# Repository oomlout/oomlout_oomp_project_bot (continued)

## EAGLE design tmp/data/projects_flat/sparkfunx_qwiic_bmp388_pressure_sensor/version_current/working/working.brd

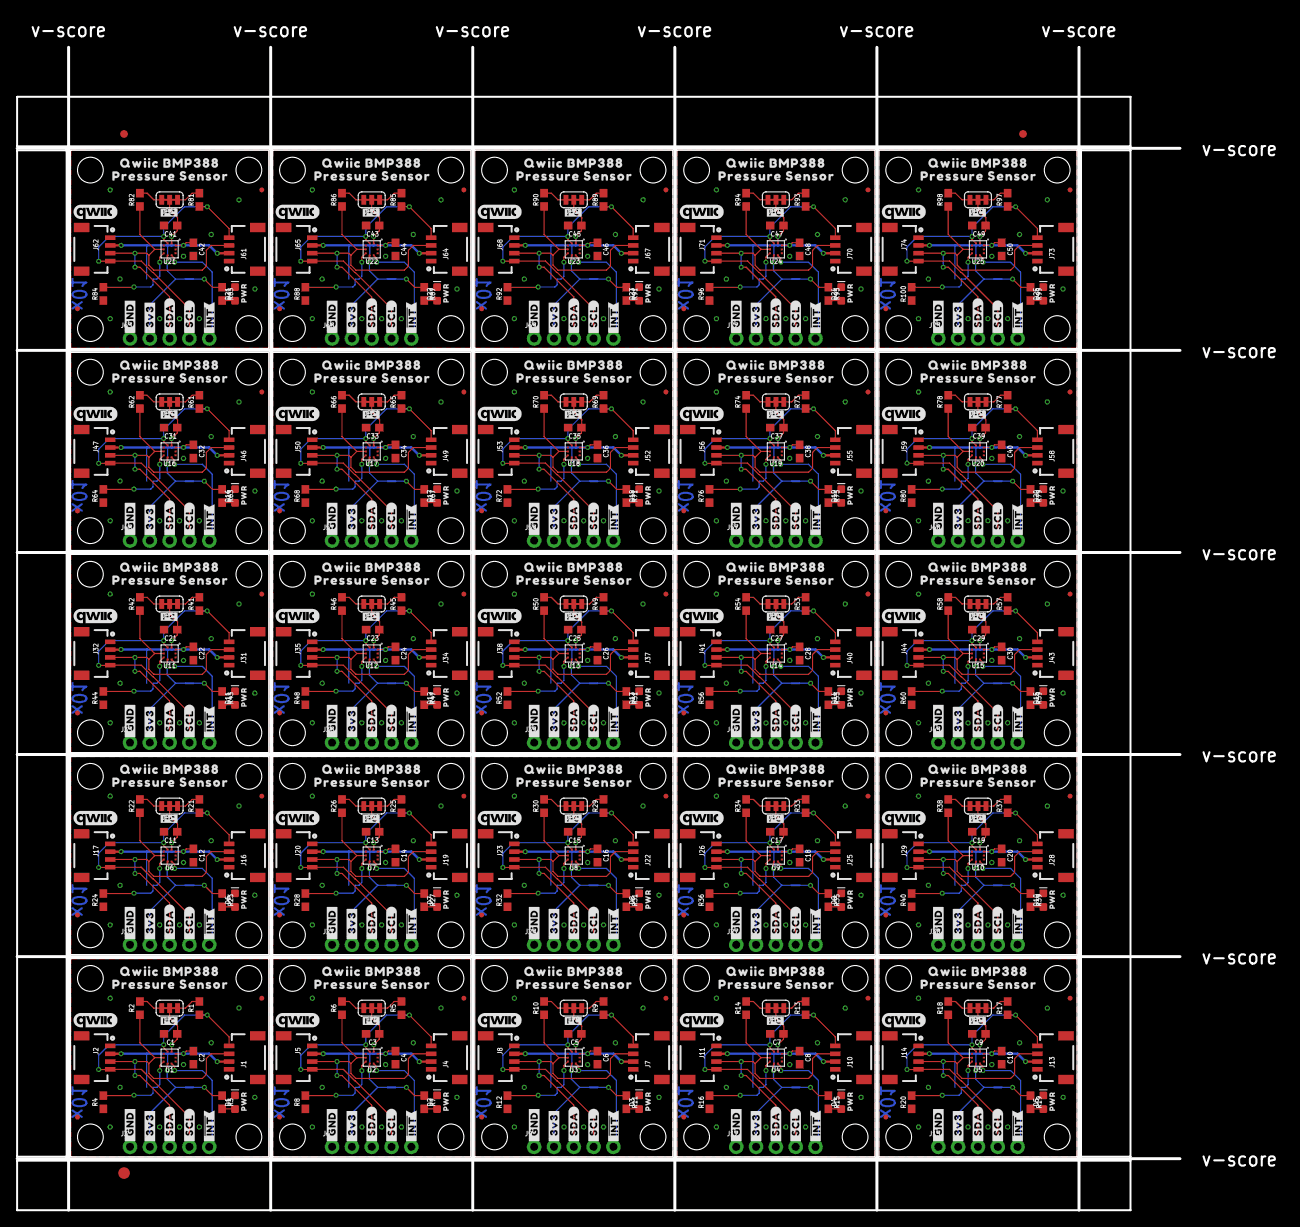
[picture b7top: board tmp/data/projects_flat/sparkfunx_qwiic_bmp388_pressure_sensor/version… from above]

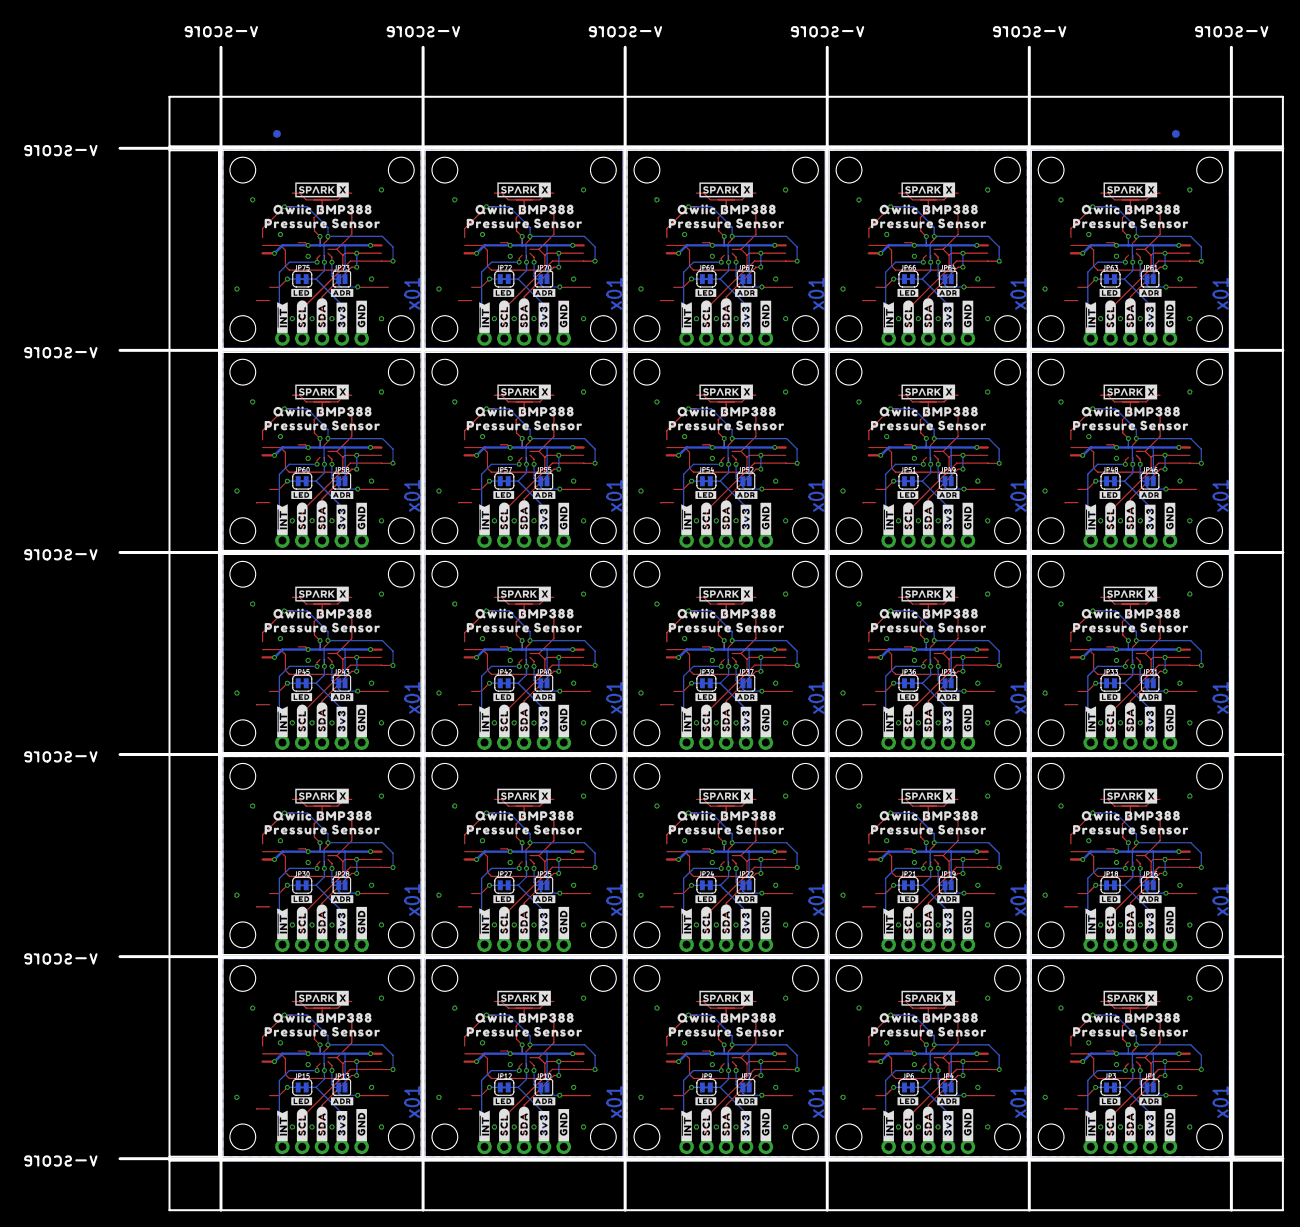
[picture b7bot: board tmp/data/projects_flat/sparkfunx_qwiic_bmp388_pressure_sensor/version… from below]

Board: 2 copper layers, 149.1 x 149.1 mm, 955 parts (302 on the bottom side), 250 nets.

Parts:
A1, A2, A3, A4, A5, A6, A7, A8, A9, A10, A11, A12, A13, A14, A15, A16, A17, A18, A19, A20, A21, A22, A23, A24, A25: QWIIC_BOARD_OUTLINEH; QWIIC_BOARD_MOUNT_HOLES
C1, C2, C3, C4, C5, C6, C7, C8, C9, C10, C11, C12, C13, C14, C15, C16, C17, C18, C19, C20, C21, C22, C23, C24, C25, C26, C27, C28, C29, C30, C31, C32, C33, C34, C35, C36, C37, C38, C39, C40, C41, C42, C43, C44, C45, C46, C47, C48, C49, C50: 0.1uF; 0603
D1, D2, D3, D4, D5, D6, D7, D8, D9, D10, D11, D12, D13, D14, D15, D16, D17, D18, D19, D20, D21, D22, D23, D24, D25: RED; LED-0603
E$1, E$2, E$3, E$4: FIDUCIAL-1X2
E$5: FIDUCIAL-1.5X3
FD1, FD2, FD3, FD4, FD5, FD6, FD7, FD8, FD9, FD10, FD11, FD12, FD13, FD14, FD15, FD16, FD17, FD18, FD19, FD20, FD21, FD22, FD23, FD24, FD25, FD26, FD27, FD28, FD29, FD30, FD31, FD32, FD33, FD34, FD35, FD36, FD37, FD38, FD39, FD40, FD41, FD42, FD43, FD44, FD45, FD46, FD47, FD48, FD49, FD50: FIDUCIALUFIDUCIAL; FIDUCIAL-MICRO
FRAME1, FRAME2, FRAME3, FRAME4, FRAME5, FRAME6, FRAME7, FRAME8, FRAME9, FRAME10, FRAME11, FRAME12, FRAME13, FRAME14, FRAME15, FRAME16, FRAME17, FRAME18, FRAME19, FRAME20, FRAME21, FRAME22, FRAME23, FRAME24, FRAME25: FRAME-LETTERNO_PACKAGE; DUMMY
J1, J2, J4, J5, J7, J8, J10, J11, J13, J14, J16, J17, J19, J20, J22, J23, J25, J26, J28, J29, J31, J32, J34, J35, J37, J38, J40, J41, J43, J44, J46, J47, J49, J50, J52, J53, J55, J56, J58, J59, J61, J62, J64, J65, J67, J68, J70, J71, J73, J74: 1X04_1MM_RA
J3, J6, J9, J12, J15, J18, J21, J24, J27, J30, J33, J36, J39, J42, J45, J48, J51, J54, J57, J60, J63, J66, J69, J72, J75: 1X05_NO_SILK
JP1, JP4, JP7, JP10, JP13, JP16, JP19, JP22, JP25, JP28, JP31, JP34, JP37, JP40, JP43, JP46, JP49, JP52, JP55, JP58, JP61, JP64, JP67, JP70, JP73: SMT-JUMPER_2_NO_SILK
JP2, JP5, JP8, JP11, JP14, JP17, JP20, JP23, JP26, JP29, JP32, JP35, JP38, JP41, JP44, JP47, JP50, JP53, JP56, JP59, JP62, JP65, JP68, JP71, JP74: SMT-JUMPER_3_2-NC_TRACE_SILK
JP3, JP6, JP9, JP12, JP15, JP18, JP21, JP24, JP27, JP30, JP33, JP36, JP39, JP42, JP45, JP48, JP51, JP54, JP57, JP60, JP63, JP66, JP69, JP72, JP75: SMT-JUMPER_2_NC_TRACE_SILK
R1, R2, R5, R6, R9, R10, R13, R14, R17, R18, R21, R22, R25, R26, R29, R30, R33, R34, R37, R38, R41, R42, R45, R46, R49, R50, R53, R54, R57, R58, R61, R62, R65, R66, R69, R70, R73, R74, R77, R78, R81, R82, R85, R86, R89, R90, R93, R94, R97, R98: 2.2k; 0603
R3, R7, R11, R15, R19, R23, R27, R31, R35, R39, R43, R47, R51, R55, R59, R63, R67, R71, R75, R79, R83, R87, R91, R95, R99: 1k; 0603
R4, R8, R12, R16, R20, R24, R28, R32, R36, R40, R44, R48, R52, R56, R60, R64, R68, R72, R76, R80, R84, R88, R92, R96, R100: 10k; 0603
U1, U2, U3, U4, U5, U6, U7, U8, U9, U10, U11, U12, U13, U14, U15, U16, U17, U18, U19, U20, U21, U22, U23, U24, U25: BMP388BMP388; LGA-10(2X2)
U$1, U$13, U$21, U$33, U$41, U$53, U$61, U$73, U$81, U$93, U$101, U$113, U$121, U$133, U$141, U$153, U$161, U$173, U$181, U$193, U$201, U$213, U$221, U$233, U$241, U$253, U$261, U$273, U$281, U$293, U$301, U$313, U$321, U$333, U$341, U$353, U$361, U$373, U$381, U$393, U$401, U$413, U$421, U$433, U$441, U$453, U$461, U$473, U$481, U$493: #_GND#3889
U$2, U$12, U$22, U$32, U$42, U$52, U$62, U$72, U$82, U$92, U$102, U$112, U$122, U$132, U$142, U$152, U$162, U$172, U$182, U$192, U$202, U$212, U$222, U$232, U$242, U$252, U$262, U$272, U$282, U$292, U$302, U$312, U$322, U$332, U$342, U$352, U$362, U$372, U$382, U$392, U$402, U$412, U$422, U$432, U$442, U$452, U$462, U$472, U$482, U$492: #_3V3#3890
U$3, U$11, U$23, U$31, U$43, U$51, U$63, U$71, U$83, U$91, U$103, U$111, U$123, U$131, U$143, U$151, U$163, U$171, U$183, U$191, U$203, U$211, U$223, U$231, U$243, U$251, U$263, U$271, U$283, U$291, U$303, U$311, U$323, U$331, U$343, U$351, U$363, U$371, U$383, U$391, U$403, U$411, U$423, U$431, U$443, U$451, U$463, U$471, U$483, U$491: #_SDA#3891
U$4, U$10, U$24, U$30, U$44, U$50, U$64, U$70, U$84, U$90, U$104, U$110, U$124, U$130, U$144, U$150, U$164, U$170, U$184, U$190, U$204, U$210, U$224, U$230, U$244, U$250, U$264, U$270, U$284, U$290, U$304, U$310, U$324, U$330, U$344, U$350, U$364, U$370, U$384, U$390, U$404, U$410, U$424, U$430, U$444, U$450, U$464, U$470, U$484, U$490: #_SCL#3892
U$5, U$9, U$25, U$29, U$45, U$49, U$65, U$69, U$85, U$89, U$105, U$109, U$125, U$129, U$145, U$149, U$165, U$169, U$185, U$189, U$205, U$209, U$225, U$229, U$245, U$249, U$265, U$269, U$285, U$289, U$305, U$309, U$325, U$329, U$345, U$349, U$365, U$369, U$385, U$389, U$405, U$409, U$425, U$429, U$445, U$449, U$465, U$469, U$485, U$489: #_#INT##3893
U$6, U$26, U$46, U$66, U$86, U$106, U$126, U$146, U$166, U$186, U$206, U$226, U$246, U$266, U$286, U$306, U$326, U$346, U$366, U$386, U$406, U$426, U$446, U$466, U$486: #I�C#1
U$7, U$27, U$47, U$67, U$87, U$107, U$127, U$147, U$167, U$187, U$207, U$227, U$247, U$267, U$287, U$307, U$327, U$347, U$367, U$387, U$407, U$427, U$447, U$467, U$487: #ADR#2
U$8, U$28, U$48, U$68, U$88, U$108, U$128, U$148, U$168, U$188, U$208, U$228, U$248, U$268, U$288, U$308, U$328, U$348, U$368, U$388, U$408, U$428, U$448, U$468, U$488: #LED#0
U$14, U$17, U$34, U$37, U$54, U$57, U$74, U$77, U$94, U$97, U$114, U$117, U$134, U$137, U$154, U$157, U$174, U$177, U$194, U$197, U$214, U$217, U$234, U$237, U$254, U$257, U$274, U$277, U$294, U$297, U$314, U$317, U$334, U$337, U$354, U$357, U$374, U$377, U$394, U$397, U$414, U$417, U$434, U$437, U$454, U$457, U$474, U$477, U$494, U$497: QWIIC_BMP3888
U$15, U$18, U$35, U$38, U$55, U$58, U$75, U$78, U$95, U$98, U$115, U$118, U$135, U$138, U$155, U$158, U$175, U$178, U$195, U$198, U$215, U$218, U$235, U$238, U$255, U$258, U$275, U$278, U$295, U$298, U$315, U$318, U$335, U$338, U$355, U$358, U$375, U$378, U$395, U$398, U$415, U$418, U$435, U$438, U$455, U$458, U$475, U$478, U$495, U$498: PRESSURE_SENSOR9
U$16, U$36, U$56, U$76, U$96, U$116, U$136, U$156, U$176, U$196, U$216, U$236, U$256, U$276, U$296, U$316, U$336, U$356, U$376, U$396, U$416, U$436, U$456, U$476, U$496: QWIIC_COPYRIGHT_SMALL
U$19, U$39, U$59, U$79, U$99, U$119, U$139, U$159, U$179, U$199, U$219, U$239, U$259, U$279, U$299, U$319, U$339, U$359, U$379, U$399, U$419, U$439, U$459, U$479, U$499: SPARKX-SMALL
U$20, U$40, U$60, U$80, U$100, U$120, U$140, U$160, U$180, U$200, U$220, U$240, U$260, U$280, U$300, U$320, U$340, U$360, U$380, U$400, U$420, U$440, U$460, U$480, U$500: PWR0

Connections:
3.3V: C1.1, C2.1, J1.2, J2.2, J3.2, JP1.2, JP2.2, JP3.2, U1.1, U1.6, U1.10
3.3V1: C3.1, C4.1, J4.2, J5.2, J6.2, JP4.2, JP5.2, JP6.2, U2.1, U2.6, U2.10
3.3V2: C5.1, C6.1, J7.2, J8.2, J9.2, JP7.2, JP8.2, JP9.2, U3.1, U3.6, U3.10
3.3V3: C7.1, C8.1, J10.2, J11.2, J12.2, JP10.2, JP11.2, JP12.2, U4.1, U4.6, U4.10
3.3V4: C9.1, C10.1, J13.2, J14.2, J15.2, JP13.2, JP14.2, JP15.2, U5.1, U5.6, U5.10
3.3V5: C11.1, C12.1, J16.2, J17.2, J18.2, JP16.2, JP17.2, JP18.2, U6.1, U6.6, U6.10
3.3V6: C13.1, C14.1, J19.2, J20.2, J21.2, JP19.2, JP20.2, JP21.2, U7.1, U7.6, U7.10
3.3V7: C15.1, C16.1, J22.2, J23.2, J24.2, JP22.2, JP23.2, JP24.2, U8.1, U8.6, U8.10
3.3V8: C17.1, C18.1, J25.2, J26.2, J27.2, JP25.2, JP26.2, JP27.2, U9.1, U9.6, U9.10
3.3V9: C19.1, C20.1, J28.2, J29.2, J30.2, JP28.2, JP29.2, JP30.2, U10.1, U10.6, U10.10
3.3V10: C21.1, C22.1, J31.2, J32.2, J33.2, JP31.2, JP32.2, JP33.2, U11.1, U11.6, U11.10
3.3V11: C23.1, C24.1, J34.2, J35.2, J36.2, JP34.2, JP35.2, JP36.2, U12.1, U12.6, U12.10
3.3V12: C25.1, C26.1, J37.2, J38.2, J39.2, JP37.2, JP38.2, JP39.2, U13.1, U13.6, U13.10
3.3V13: C27.1, C28.1, J40.2, J41.2, J42.2, JP40.2, JP41.2, JP42.2, U14.1, U14.6, U14.10
3.3V14: C29.1, C30.1, J43.2, J44.2, J45.2, JP43.2, JP44.2, JP45.2, U15.1, U15.6, U15.10
3.3V15: C31.1, C32.1, J46.2, J47.2, J48.2, JP46.2, JP47.2, JP48.2, U16.1, U16.6, U16.10
3.3V16: C33.1, C34.1, J49.2, J50.2, J51.2, JP49.2, JP50.2, JP51.2, U17.1, U17.6, U17.10
3.3V17: C35.1, C36.1, J52.2, J53.2, J54.2, JP52.2, JP53.2, JP54.2, U18.1, U18.6, U18.10
3.3V18: C37.1, C38.1, J55.2, J56.2, J57.2, JP55.2, JP56.2, JP57.2, U19.1, U19.6, U19.10
3.3V19: C39.1, C40.1, J58.2, J59.2, J60.2, JP58.2, JP59.2, JP60.2, U20.1, U20.6, U20.10
3.3V20: C41.1, C42.1, J61.2, J62.2, J63.2, JP61.2, JP62.2, JP63.2, U21.1, U21.6, U21.10
3.3V21: C43.1, C44.1, J64.2, J65.2, J66.2, JP64.2, JP65.2, JP66.2, U22.1, U22.6, U22.10
3.3V22: C45.1, C46.1, J67.2, J68.2, J69.2, JP67.2, JP68.2, JP69.2, U23.1, U23.6, U23.10
3.3V23: C47.1, C48.1, J70.2, J71.2, J72.2, JP70.2, JP71.2, JP72.2, U24.1, U24.6, U24.10
3.3V24: C49.1, C50.1, J73.2, J74.2, J75.2, JP73.2, JP74.2, JP75.2, U25.1, U25.6, U25.10
ADR: JP1.1, R4.2, U1.5
ADR1: JP4.1, R8.2, U2.5
ADR2: JP7.1, R12.2, U3.5
ADR3: JP10.1, R16.2, U4.5
ADR4: JP13.1, R20.2, U5.5
ADR5: JP16.1, R24.2, U6.5
ADR6: JP19.1, R28.2, U7.5
ADR7: JP22.1, R32.2, U8.5
ADR8: JP25.1, R36.2, U9.5
ADR9: JP28.1, R40.2, U10.5
ADR10: JP31.1, R44.2, U11.5
ADR11: JP34.1, R48.2, U12.5
ADR12: JP37.1, R52.2, U13.5
ADR13: JP40.1, R56.2, U14.5
ADR14: JP43.1, R60.2, U15.5
ADR15: JP46.1, R64.2, U16.5
ADR16: JP49.1, R68.2, U17.5
ADR17: JP52.1, R72.2, U18.5
ADR18: JP55.1, R76.2, U19.5
ADR19: JP58.1, R80.2, U20.5
ADR20: JP61.1, R84.2, U21.5
ADR21: JP64.1, R88.2, U22.5
ADR22: JP67.1, R92.2, U23.5
ADR23: JP70.1, R96.2, U24.5
ADR24: JP73.1, R100.2, U25.5
GND: C1.2, C2.2, D1.C, J1.1, J2.1, J3.1, R4.1, U1.3, U1.8, U1.9
GND1: C3.2, C4.2, D2.C, J4.1, J5.1, J6.1, R8.1, U2.3, U2.8, U2.9
GND2: C5.2, C6.2, D3.C, J7.1, J8.1, J9.1, R12.1, U3.3, U3.8, U3.9
GND3: C7.2, C8.2, D4.C, J10.1, J11.1, J12.1, R16.1, U4.3, U4.8, U4.9
GND4: C9.2, C10.2, D5.C, J13.1, J14.1, J15.1, R20.1, U5.3, U5.8, U5.9
GND5: C11.2, C12.2, D6.C, J16.1, J17.1, J18.1, R24.1, U6.3, U6.8, U6.9
GND6: C13.2, C14.2, D7.C, J19.1, J20.1, J21.1, R28.1, U7.3, U7.8, U7.9
GND7: C15.2, C16.2, D8.C, J22.1, J23.1, J24.1, R32.1, U8.3, U8.8, U8.9
GND8: C17.2, C18.2, D9.C, J25.1, J26.1, J27.1, R36.1, U9.3, U9.8, U9.9
GND9: C19.2, C20.2, D10.C, J28.1, J29.1, J30.1, R40.1, U10.3, U10.8, U10.9
GND10: C21.2, C22.2, D11.C, J31.1, J32.1, J33.1, R44.1, U11.3, U11.8, U11.9
GND11: C23.2, C24.2, D12.C, J34.1, J35.1, J36.1, R48.1, U12.3, U12.8, U12.9
GND12: C25.2, C26.2, D13.C, J37.1, J38.1, J39.1, R52.1, U13.3, U13.8, U13.9
GND13: C27.2, C28.2, D14.C, J40.1, J41.1, J42.1, R56.1, U14.3, U14.8, U14.9
GND14: C29.2, C30.2, D15.C, J43.1, J44.1, J45.1, R60.1, U15.3, U15.8, U15.9
GND15: C31.2, C32.2, D16.C, J46.1, J47.1, J48.1, R64.1, U16.3, U16.8, U16.9
GND16: C33.2, C34.2, D17.C, J49.1, J50.1, J51.1, R68.1, U17.3, U17.8, U17.9
GND17: C35.2, C36.2, D18.C, J52.1, J53.1, J54.1, R72.1, U18.3, U18.8, U18.9
GND18: C37.2, C38.2, D19.C, J55.1, J56.1, J57.1, R76.1, U19.3, U19.8, U19.9
GND19: C39.2, C40.2, D20.C, J58.1, J59.1, J60.1, R80.1, U20.3, U20.8, U20.9
GND20: C41.2, C42.2, D21.C, J61.1, J62.1, J63.1, R84.1, U21.3, U21.8, U21.9
GND21: C43.2, C44.2, D22.C, J64.1, J65.1, J66.1, R88.1, U22.3, U22.8, U22.9
GND22: C45.2, C46.2, D23.C, J67.1, J68.1, J69.1, R92.1, U23.3, U23.8, U23.9
GND23: C47.2, C48.2, D24.C, J70.1, J71.1, J72.1, R96.1, U24.3, U24.8, U24.9
GND24: C49.2, C50.2, D25.C, J73.1, J74.1, J75.1, R100.1, U25.3, U25.8, U25.9
INT: J3.5, U1.7
INT1: J6.5, U2.7
INT2: J9.5, U3.7
INT3: J12.5, U4.7
INT4: J15.5, U5.7
INT5: J18.5, U6.7
INT6: J21.5, U7.7
INT7: J24.5, U8.7
INT8: J27.5, U9.7
INT9: J30.5, U10.7
INT10: J33.5, U11.7
INT11: J36.5, U12.7
INT12: J39.5, U13.7
INT13: J42.5, U14.7
INT14: J45.5, U15.7
INT15: J48.5, U16.7
INT16: J51.5, U17.7
INT17: J54.5, U18.7
INT18: J57.5, U19.7
INT19: J60.5, U20.7
INT20: J63.5, U21.7
INT21: J66.5, U22.7
INT22: J69.5, U23.7
INT23: J72.5, U24.7
INT24: J75.5, U25.7
unnamed: JP2.3, R2.2
unnamed: JP2.1, R1.2
unnamed: JP5.3, R6.2
unnamed: JP3.1, R3.1
unnamed: D1.A, R3.2
unnamed: JP5.1, R5.2
unnamed: JP6.1, R7.1
unnamed: D2.A, R7.2
unnamed: JP8.3, R10.2
unnamed: JP8.1, R9.2
unnamed: JP9.1, R11.1
unnamed: D3.A, R11.2
unnamed: JP11.3, R14.2
unnamed: JP11.1, R13.2
unnamed: JP12.1, R15.1
unnamed: D4.A, R15.2
unnamed: JP14.3, R18.2
unnamed: JP14.1, R17.2
unnamed: JP15.1, R19.1
unnamed: D5.A, R19.2
unnamed: JP17.3, R22.2
unnamed: JP17.1, R21.2
unnamed: JP18.1, R23.1
unnamed: D6.A, R23.2
unnamed: JP20.3, R26.2
unnamed: JP20.1, R25.2
unnamed: JP21.1, R27.1
unnamed: D7.A, R27.2
unnamed: JP23.3, R30.2
unnamed: JP23.1, R29.2
unnamed: JP24.1, R31.1
unnamed: D8.A, R31.2
unnamed: JP26.3, R34.2
unnamed: JP26.1, R33.2
unnamed: JP27.1, R35.1
unnamed: D9.A, R35.2
unnamed: JP29.3, R38.2
unnamed: JP29.1, R37.2
unnamed: JP30.1, R39.1
unnamed: D10.A, R39.2
unnamed: JP32.3, R42.2
unnamed: JP32.1, R41.2
unnamed: JP33.1, R43.1
unnamed: D11.A, R43.2
unnamed: JP35.3, R46.2
unnamed: JP35.1, R45.2
unnamed: JP36.1, R47.1
unnamed: D12.A, R47.2
unnamed: JP38.3, R50.2
unnamed: JP38.1, R49.2
unnamed: JP39.1, R51.1
unnamed: D13.A, R51.2
unnamed: JP41.3, R54.2
unnamed: JP41.1, R53.2
unnamed: JP42.1, R55.1
unnamed: D14.A, R55.2
unnamed: JP44.3, R58.2
unnamed: JP44.1, R57.2
unnamed: JP45.1, R59.1
unnamed: D15.A, R59.2
unnamed: JP47.3, R62.2
unnamed: JP47.1, R61.2
unnamed: JP48.1, R63.1
unnamed: D16.A, R63.2
unnamed: JP50.3, R66.2
unnamed: JP50.1, R65.2
unnamed: JP51.1, R67.1
unnamed: D17.A, R67.2
unnamed: JP53.3, R70.2
unnamed: JP53.1, R69.2
unnamed: JP54.1, R71.1
unnamed: D18.A, R71.2
unnamed: JP56.3, R74.2
unnamed: JP56.1, R73.2
unnamed: JP57.1, R75.1
unnamed: D19.A, R75.2
unnamed: JP59.3, R78.2
unnamed: JP59.1, R77.2
unnamed: JP60.1, R79.1
unnamed: D20.A, R79.2
unnamed: JP62.3, R82.2
unnamed: JP62.1, R81.2
unnamed: JP63.1, R83.1
unnamed: D21.A, R83.2
unnamed: JP65.3, R86.2
unnamed: JP65.1, R85.2
unnamed: JP66.1, R87.1
unnamed: D22.A, R87.2
unnamed: JP68.3, R90.2
unnamed: JP68.1, R89.2
unnamed: JP69.1, R91.1
unnamed: D23.A, R91.2
unnamed: JP71.3, R94.2
unnamed: JP71.1, R93.2
unnamed: JP72.1, R95.1
unnamed: D24.A, R95.2
unnamed: JP74.3, R98.2
unnamed: JP74.1, R97.2
unnamed: JP75.1, R99.1
unnamed: D25.A, R99.2
SCL: J1.4, J2.4, J3.4, R1.1, U1.2
SCL1: J4.4, J5.4, J6.4, R5.1, U2.2
SCL2: J7.4, J8.4, J9.4, R9.1, U3.2
SCL3: J10.4, J11.4, J12.4, R13.1, U4.2
SCL4: J13.4, J14.4, J15.4, R17.1, U5.2
SCL5: J16.4, J17.4, J18.4, R21.1, U6.2
SCL6: J19.4, J20.4, J21.4, R25.1, U7.2
SCL7: J22.4, J23.4, J24.4, R29.1, U8.2
SCL8: J25.4, J26.4, J27.4, R33.1, U9.2
SCL9: J28.4, J29.4, J30.4, R37.1, U10.2
SCL10: J31.4, J32.4, J33.4, R41.1, U11.2
SCL11: J34.4, J35.4, J36.4, R45.1, U12.2
SCL12: J37.4, J38.4, J39.4, R49.1, U13.2
SCL13: J40.4, J41.4, J42.4, R53.1, U14.2
SCL14: J43.4, J44.4, J45.4, R57.1, U15.2
SCL15: J46.4, J47.4, J48.4, R61.1, U16.2
SCL16: J49.4, J50.4, J51.4, R65.1, U17.2
SCL17: J52.4, J53.4, J54.4, R69.1, U18.2
SCL18: J55.4, J56.4, J57.4, R73.1, U19.2
SCL19: J58.4, J59.4, J60.4, R77.1, U20.2
SCL20: J61.4, J62.4, J63.4, R81.1, U21.2
SCL21: J64.4, J65.4, J66.4, R85.1, U22.2
SCL22: J67.4, J68.4, J69.4, R89.1, U23.2
SCL23: J70.4, J71.4, J72.4, R93.1, U24.2
SCL24: J73.4, J74.4, J75.4, R97.1, U25.2
SDA: J1.3, J2.3, J3.3, R2.1, U1.4
SDA1: J4.3, J5.3, J6.3, R6.1, U2.4
SDA2: J7.3, J8.3, J9.3, R10.1, U3.4
SDA3: J10.3, J11.3, J12.3, R14.1, U4.4
SDA4: J13.3, J14.3, J15.3, R18.1, U5.4
SDA5: J16.3, J17.3, J18.3, R22.1, U6.4
SDA6: J19.3, J20.3, J21.3, R26.1, U7.4
SDA7: J22.3, J23.3, J24.3, R30.1, U8.4
SDA8: J25.3, J26.3, J27.3, R34.1, U9.4
SDA9: J28.3, J29.3, J30.3, R38.1, U10.4
SDA10: J31.3, J32.3, J33.3, R42.1, U11.4
SDA11: J34.3, J35.3, J36.3, R46.1, U12.4
SDA12: J37.3, J38.3, J39.3, R50.1, U13.4
SDA13: J40.3, J41.3, J42.3, R54.1, U14.4
SDA14: J43.3, J44.3, J45.3, R58.1, U15.4
SDA15: J46.3, J47.3, J48.3, R62.1, U16.4
SDA16: J49.3, J50.3, J51.3, R66.1, U17.4
SDA17: J52.3, J53.3, J54.3, R70.1, U18.4
SDA18: J55.3, J56.3, J57.3, R74.1, U19.4
SDA19: J58.3, J59.3, J60.3, R78.1, U20.4
SDA20: J61.3, J62.3, J63.3, R82.1, U21.4
SDA21: J64.3, J65.3, J66.3, R86.1, U22.4
SDA22: J67.3, J68.3, J69.3, R90.1, U23.4
SDA23: J70.3, J71.3, J72.3, R94.1, U24.4
SDA24: J73.3, J74.3, J75.3, R98.1, U25.4
